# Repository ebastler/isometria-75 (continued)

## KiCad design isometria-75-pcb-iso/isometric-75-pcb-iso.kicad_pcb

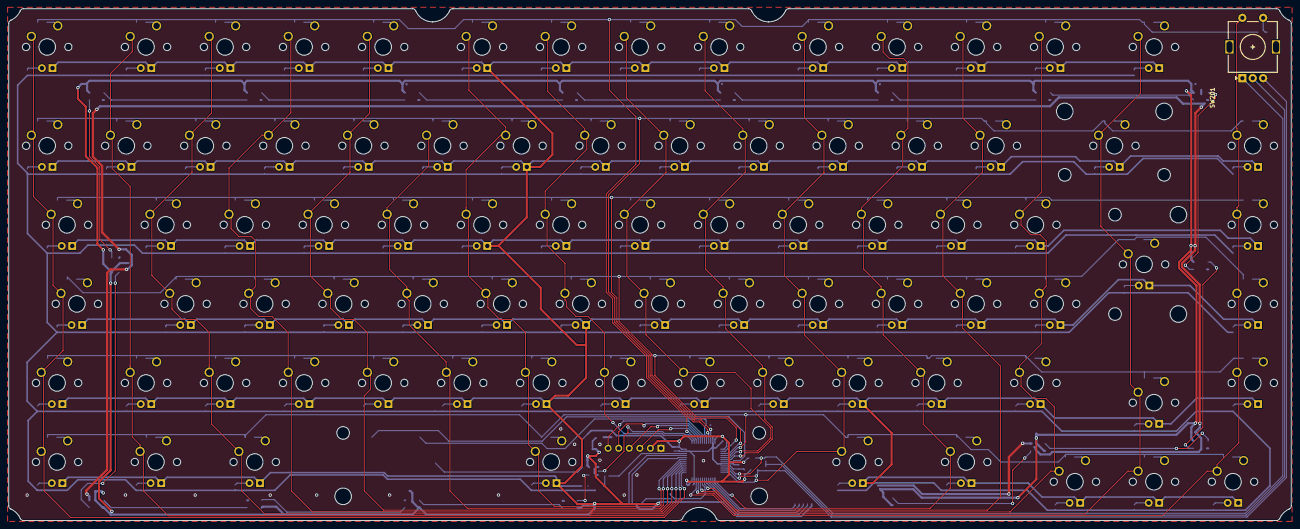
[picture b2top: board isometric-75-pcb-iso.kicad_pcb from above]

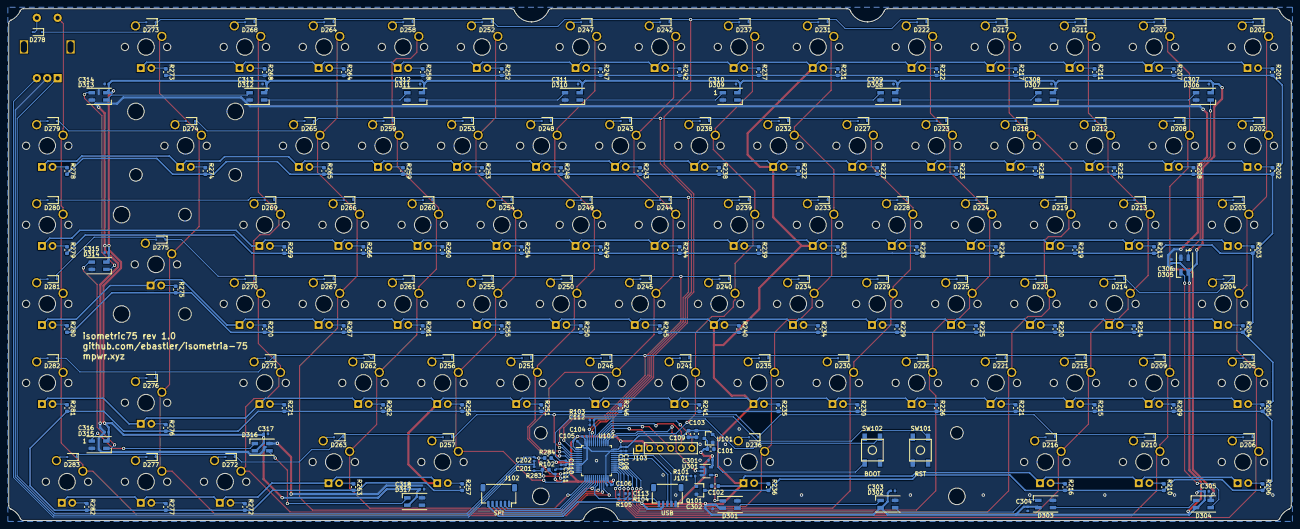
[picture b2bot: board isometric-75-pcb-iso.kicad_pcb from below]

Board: 2 copper layers, 308.3 x 123.0 mm, 314 parts (231 on the bottom side), 228 nets.

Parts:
C101, C102, C103, C109: 1u; C_0603_1608Metric
C104, C105, C106, C107, C110, C111, C112, C113, C201, C202, C301, C302, C303, C304, C305, C306, C307, C308, C309, C310, C311, C312, C313, C314, C315, C316, C317, C318: 100n; C_0402_1005Metric
C108: 1u; C_0402_1005Metric
D201, D202, D203, D204, D205, D206, D207, D208, D209, D210, D211, D212, D213, D214, D215, D216, D217, D218, D219, D220, D221, D222, D223, D224, D225, D226, D227, D228, D229, D230, D231, D232, D233, D234, D235, D236, D237, D238, D239, D240, D241, D242, D243, D244, D245, D246, D247, D248, D249, D250, D251, D252, D253, D254, D255, D256, D257, D258, D259, D260, D261, D262, D263, D264, D265, D266, D267, D268, D269, D270, D271, D272, D273, D274, D275, D276, D277, D278, D279, D280, D281, D282, D283: 1N4148; D_SOD-323F
D301, D302, D303, D304, D305, D306, D307, D308, D309, D310, D311, D312, D313, D314, D315, D316, D317: SK6812MINI; LED_SK6812MINI_PLCC4_3.5x3.5mm_P1.75mm
J101: USB; JST_SH_SM05B-SRSS-TB_1x05-1MP_P1.00mm_Horizontal
J102: SPI; JST_SH_SM06B-SRSS-TB_1x06-1MP_P1.00mm_Horizontal
J103: Conn_01x06_Male; PinHeader_1x06_P2.54mm_Vertical
MX201, MX202, MX207, MX208, MX209, MX211, MX212, MX213, MX214, MX215, MX217, MX218, MX219, MX220, MX221, MX222, MX223, MX224, MX225, MX226, MX227, MX228, MX229, MX230, MX231, MX232, MX233, MX234, MX235, MX237, MX238, MX239, MX240, MX241, MX242, MX243, MX244, MX245, MX246, MX247, MX248, MX249, MX250, MX251, MX252, MX253, MX254, MX255, MX256, MX258, MX259, MX260, MX261, MX262, MX264, MX265, MX266, MX267, MX268, MX269, MX270, MX272, MX273, MX276, MX277, MX278, MX279, MX280, MX281, MX282: MX-LED; MXOnly-1U
MX203, MX257, MX271: MX-LED; MXOnly-1.5U
MX204: MX-LED; MXOnly-1.75U
MX205, MX206, MX210, MX216, MX263: MX-LED; MXOnly-1.25U
MX236: MX-LED; MXOnly-6.25U
MX274: MX-LED; MXOnly-2U-ReversedStabilizers
MX275: MX-LED; MXOnly-ISO
Q101: AO3400A; SOT-23
R101, R102: 100; R_0402_1005Metric
R103: 10k; R_0402_1005Metric
R104, R105: 50k; R_0402_1005Metric
R201, R202, R203, R204, R205, R206, R207, R208, R209, R210, R211, R212, R213, R214, R215, R216, R217, R218, R219, R220, R221, R222, R223, R224, R225, R226, R227, R228, R229, R230, R231, R232, R233, R234, R235, R236, R237, R238, R239, R240, R241, R242, R243, R244, R245, R246, R247, R248, R249, R250, R251, R252, R253, R254, R255, R256, R257, R258, R259, R260, R261, R262, R263, R264, R265, R266, R267, R268, R269, R270, R271, R272, R273, R274, R275, R276, R277, R278, R279, R280, R281, R282: 680; R_0603_1608Metric
R283, R284: 10k; R_0603_1608Metric
SW101: RST; SKQG-1155865
SW102: BOOT; SKQG-1155865
SW201: Rotary_Encoder_Switch; RotaryEncoder_Alps_EC11E-Switch_Vertical_H20mm
U101: XC6206P332MR; SOT-23
U102: STM32F072CBTx; LQFP-48_7x7mm_P0.5mm
U301: 74LVC1G125; SOT-23-5

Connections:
+3V3: C103.1, C104.1, C105.1, C106.1, C107.1, C108.1, C109.1, J103.2, R102.1, R283.1, R284.2, SW102.1, U101.2, U102.1, U102.24, U102.36, U102.48
+5V: C101.1, C102.1, C301.1, C302.1, C303.1, C304.1, C305.1, C306.1, C307.1, C308.1, C309.1, C310.1, C311.1, C312.1, C313.1, C314.1, C315.1, C316.1, C317.1, C318.1, D301.4, D302.4, D303.4, D304.4, D305.4, D306.4, D307.4, D308.4, D309.4, D310.4, D311.4, D312.4, D313.4, D314.4, D315.4, D316.4, D317.4, J101.4, J102.6, MX201.4, MX202.4, MX203.4, MX204.4, MX205.4, MX206.4, MX207.4, MX208.4, MX209.4, MX210.4, MX211.4, MX212.4, MX213.4, MX214.4, MX215.4, MX216.4, MX217.4, MX218.4, MX219.4, MX220.4, MX221.4, MX222.4, MX223.4, MX224.4, MX225.4, MX226.4, MX227.4, MX228.4, MX229.4, MX230.4, MX231.4, MX232.4, MX233.4, MX234.4, MX235.4, MX236.4, MX237.4, MX238.4, MX239.4, MX240.4, MX241.4, MX242.4, MX243.4, MX244.4, MX245.4, MX246.4, MX247.4, MX248.4, MX249.4, MX250.4, MX251.4, MX252.4, MX253.4, MX254.4, MX255.4, MX256.4, MX257.4, MX258.4, MX259.4, MX260.4, MX261.4, MX262.4, MX263.4, MX264.4, MX265.4, MX266.4, MX267.4, MX268.4, MX269.4, MX270.4, MX271.4, MX272.4, MX273.4, MX274.4, MX275.4, MX276.4, MX277.4, MX278.4, MX279.4, MX280.4, MX281.4, MX282.4, U101.3, U301.5
COL0: MX201.1, MX202.1, MX203.1, MX204.1, MX205.1, MX206.1, U102.25
COL1: MX207.1, MX208.1, MX209.1, MX210.1, U102.26
COL2: MX211.1, MX212.1, MX213.1, MX214.1, MX215.1, MX216.1, U102.27
COL3: MX217.1, MX218.1, MX219.1, MX220.1, MX221.1, U102.28
COL4: MX222.1, MX223.1, MX224.1, MX225.1, MX226.1, U102.29
COL5: MX227.1, MX228.1, MX229.1, MX230.1, U102.30
COL6: MX231.1, MX232.1, MX233.1, MX234.1, MX235.1, MX236.1, U102.31
COL7: MX237.1, MX238.1, MX239.1, MX240.1, MX241.1, U102.37
COL8: MX242.1, MX243.1, MX244.1, MX245.1, MX246.1, U102.5
COL9: MX247.1, MX248.1, MX249.1, MX250.1, MX251.1, U102.6
COL10: MX252.1, MX253.1, MX254.1, MX255.1, MX256.1, MX257.1, U102.12
COL11: MX258.1, MX259.1, MX260.1, MX261.1, MX262.1, MX263.1, U102.13
COL12: MX264.1, MX265.1, MX266.1, MX267.1, U102.18
COL13: MX268.1, MX269.1, MX270.1, MX271.1, MX272.1, U102.20
COL14: MX273.1, MX274.1, MX275.1, MX276.1, MX277.1, U102.21
COL15: MX278.1, MX279.1, MX280.1, MX281.1, MX282.1, SW201.S2, U102.22
GND: C101.2, C102.2, C103.2, C104.2, C105.2, C106.2, C107.2, C108.2, C109.2, C110.2, C111.2, C112.2, C113.2, C201.1, C202.2, C301.2, C302.2, C303.2, C304.2, C305.2, C306.2, C307.2, C308.2, C309.2, C310.2, C311.2, C312.2, C313.2, C314.2, C315.2, C316.2, C317.2, C318.2, D301.2, D302.2, D303.2, D304.2, D305.2, D306.2, D307.2, D308.2, D309.2, D310.2, D311.2, D312.2, D313.2, D314.2, D315.2, D316.2, D317.2, J101.1, J102.1, J103.1, Q101.2, R103.2, R105.2, SW101.1, SW201.C, U101.1, U102.8, U102.23, U102.35, U102.47, U301.1, U301.3
LED-: Q101.3, R201.2, R202.2, R203.2, R204.2, R205.2, R206.2, R207.2, R208.2, R209.2, R210.2, R211.2, R212.2, R213.2, R214.2, R215.2, R216.2, R217.2, R218.2, R219.2, R220.2, R221.2, R222.2, R223.2, R224.2, R225.2, R226.2, R227.2, R228.2, R229.2, R230.2, R231.2, R232.2, R233.2, R234.2, R235.2, R236.2, R237.2, R238.2, R239.2, R240.2, R241.2, R242.2, R243.2, R244.2, R245.2, R246.2, R247.2, R248.2, R249.2, R250.2, R251.2, R252.2, R253.2, R254.2, R255.2, R256.2, R257.2, R258.2, R259.2, R260.2, R261.2, R262.2, R263.2, R264.2, R265.2, R266.2, R267.2, R268.2, R269.2, R270.2, R271.2, R272.2, R273.2, R274.2, R275.2, R276.2, R277.2, R278.2, R279.2, R280.2, R281.2, R282.2
LED_PWM: R101.1, U102.34
unnamed: C110.1, SW101.2, U102.7
unnamed: C111.1, R102.2, U102.9
unnamed: C112.1, R103.1, SW102.2, U102.44
unnamed: C113.1, R104.2, R105.1, U102.19
unnamed: D201.2, MX201.2
unnamed: D202.2, MX202.2
unnamed: D203.2, MX203.2
unnamed: D204.2, MX204.2
unnamed: D205.2, MX205.2
unnamed: D206.2, MX206.2
unnamed: D207.2, MX207.2
unnamed: D208.2, MX208.2
unnamed: D209.2, MX209.2
unnamed: D210.2, MX210.2
unnamed: D211.2, MX211.2
unnamed: D212.2, MX212.2
unnamed: D213.2, MX213.2
unnamed: D214.2, MX214.2
unnamed: D215.2, MX215.2
unnamed: D216.2, MX216.2
unnamed: D217.2, MX217.2
unnamed: D218.2, MX218.2
unnamed: D219.2, MX219.2
unnamed: D220.2, MX220.2
unnamed: D221.2, MX221.2
unnamed: D222.2, MX222.2
unnamed: D223.2, MX223.2
unnamed: D224.2, MX224.2
unnamed: D225.2, MX225.2
unnamed: D226.2, MX226.2
unnamed: D227.2, MX227.2
unnamed: D228.2, MX228.2
unnamed: D229.2, MX229.2
unnamed: D230.2, MX230.2
unnamed: D231.2, MX231.2
unnamed: D232.2, MX232.2
unnamed: D233.2, MX233.2
unnamed: D234.2, MX234.2
unnamed: D235.2, MX235.2
unnamed: D236.2, MX236.2
unnamed: D237.2, MX237.2
unnamed: D238.2, MX238.2
unnamed: D239.2, MX239.2
unnamed: D240.2, MX240.2
unnamed: D241.2, MX241.2
unnamed: D242.2, MX242.2
unnamed: D243.2, MX243.2
unnamed: D244.2, MX244.2
unnamed: D245.2, MX245.2
unnamed: D246.2, MX246.2
unnamed: D247.2, MX247.2
unnamed: D248.2, MX248.2
unnamed: D249.2, MX249.2
unnamed: D250.2, MX250.2
unnamed: D251.2, MX251.2
unnamed: D252.2, MX252.2
unnamed: D253.2, MX253.2
unnamed: D254.2, MX254.2
unnamed: D255.2, MX255.2
unnamed: D256.2, MX256.2
unnamed: D257.2, MX257.2
unnamed: D258.2, MX258.2
unnamed: D259.2, MX259.2
unnamed: D260.2, MX260.2
unnamed: D261.2, MX261.2
unnamed: D262.2, MX262.2
unnamed: D263.2, MX263.2
unnamed: D264.2, MX264.2
unnamed: D265.2, MX265.2
unnamed: D266.2, MX266.2
unnamed: D267.2, MX267.2
unnamed: D268.2, MX268.2
unnamed: D269.2, MX269.2
unnamed: D270.2, MX270.2
unnamed: D271.2, MX271.2
unnamed: D272.2, MX272.2
unnamed: D273.2, MX273.2
unnamed: D274.2, MX274.2
unnamed: D275.2, MX275.2
unnamed: D276.2, MX276.2
unnamed: D277.2, MX277.2
unnamed: D278.2, SW201.S1
unnamed: D279.2, MX278.2
unnamed: D280.2, MX279.2
unnamed: D281.2, MX280.2
unnamed: D282.2, MX281.2
unnamed: D283.2, MX282.2
unnamed: D301.1, D302.3
unnamed: D301.3, U301.4
unnamed: D302.1, D303.3
unnamed: D303.1, D304.3
unnamed: D304.1, D305.3
unnamed: D305.1, D306.3
unnamed: D306.1, D307.3
unnamed: D307.1, D308.3
unnamed: D308.1, D309.3
unnamed: D309.1, D310.3
unnamed: D310.1, D311.3
unnamed: D311.1, D312.3
unnamed: D312.1, D313.3
unnamed: D313.1, D314.3
unnamed: D314.1, D315.3
unnamed: D315.1, D316.3
unnamed: D316.1, D317.3
unnamed: MX201.3, R201.1
unnamed: MX202.3, R202.1
unnamed: MX203.3, R203.1
unnamed: MX204.3, R204.1
unnamed: MX205.3, R205.1
unnamed: MX206.3, R206.1
unnamed: MX207.3, R207.1
unnamed: MX208.3, R208.1
unnamed: MX209.3, R209.1
unnamed: MX210.3, R210.1
unnamed: MX211.3, R211.1
unnamed: MX212.3, R212.1
unnamed: MX213.3, R213.1
unnamed: MX214.3, R214.1
unnamed: MX215.3, R215.1
unnamed: MX216.3, R216.1
unnamed: MX217.3, R217.1
unnamed: MX218.3, R218.1
unnamed: MX219.3, R219.1
unnamed: MX220.3, R220.1
unnamed: MX221.3, R221.1
unnamed: MX222.3, R222.1
unnamed: MX223.3, R223.1
unnamed: MX224.3, R224.1
unnamed: MX225.3, R225.1
unnamed: MX226.3, R226.1
unnamed: MX227.3, R227.1
unnamed: MX228.3, R228.1
unnamed: MX229.3, R229.1
unnamed: MX230.3, R230.1
unnamed: MX231.3, R231.1
unnamed: MX232.3, R232.1
unnamed: MX233.3, R233.1
unnamed: MX234.3, R234.1
unnamed: MX235.3, R235.1
unnamed: MX236.3, R236.1
unnamed: MX237.3, R237.1
unnamed: MX238.3, R238.1
unnamed: MX239.3, R239.1
unnamed: MX240.3, R240.1
unnamed: MX241.3, R241.1
unnamed: MX242.3, R242.1
unnamed: MX243.3, R243.1
unnamed: MX244.3, R244.1
unnamed: MX245.3, R245.1
unnamed: MX246.3, R246.1
unnamed: MX247.3, R247.1
unnamed: MX248.3, R248.1
unnamed: MX249.3, R249.1
unnamed: MX250.3, R250.1
unnamed: MX251.3, R251.1
unnamed: MX252.3, R252.1
unnamed: MX253.3, R253.1
unnamed: MX254.3, R254.1
unnamed: MX255.3, R255.1
unnamed: MX256.3, R256.1
unnamed: MX257.3, R257.1
unnamed: MX258.3, R258.1
unnamed: MX259.3, R259.1
unnamed: MX260.3, R260.1
unnamed: MX261.3, R261.1
unnamed: MX262.3, R262.1
unnamed: MX263.3, R263.1
unnamed: MX264.3, R264.1
unnamed: MX265.3, R265.1
unnamed: MX266.3, R266.1
unnamed: MX267.3, R267.1
unnamed: MX268.3, R268.1
unnamed: MX269.3, R269.1
unnamed: MX270.3, R270.1
unnamed: MX271.3, R271.1
unnamed: MX272.3, R272.1
unnamed: MX273.3, R273.1
unnamed: MX274.3, R274.1
unnamed: MX275.3, R275.1
unnamed: MX276.3, R276.1
unnamed: MX277.3, R277.1
unnamed: MX278.3, R278.1
unnamed: MX279.3, R279.1
unnamed: MX280.3, R280.1
unnamed: MX281.3, R281.1
unnamed: MX282.3, R282.1
unnamed: Q101.1, R101.2
PB4: J103.3, U102.40
PB5: J103.4, U102.41
PB6_TX1: J103.5, U102.42
PB7_RX1: J103.6, U102.43
ROTA: C201.2, R283.2, SW201.B, U102.11
ROTB: C202.1, R284.1, SW201.A, U102.10
ROW0: D201.1, D207.1, D211.1, D217.1, D222.1, D231.1, D237.1, D242.1, D247.1, D252.1, D258.1, D264.1, D268.1, D273.1, D278.1, U102.39
ROW1: D202.1, D208.1, D212.1, D218.1, D223.1, D227.1, D232.1, D238.1, D243.1, D248.1, D253.1, D259.1, D265.1, D274.1, D279.1, U102.45
ROW2: D203.1, D213.1, D219.1, D224.1, D228.1, D233.1, D239.1, D244.1, D249.1, D254.1, D260.1, D266.1, D269.1, D280.1, U102.46
ROW3: D204.1, D214.1, D220.1, D225.1, D229.1, D234.1, D240.1, D245.1, D250.1, D255.1, D261.1, D267.1, D270.1, D275.1, D281.1, U102.2
ROW4: D205.1, D209.1, D215.1, D221.1, D226.1, D230.1, D235.1, D241.1, D246.1, D251.1, D256.1, D262.1, D271.1, D276.1, D282.1, U102.3
ROW5: D206.1, D210.1, D216.1, D236.1, D257.1, D263.1, D272.1, D277.1, D283.1, U102.4
SPI_MISO: J102.4, U102.16
SPI_MOSI: J102.5, U102.17
SPI_NSS: J102.2, U102.14
SPI_SCK: J102.3, U102.15
UGLED: U102.38, U301.2
USB-D+: J101.2, U102.33
USB-D-: J101.3, U102.32
Vsense: J101.5, R104.1

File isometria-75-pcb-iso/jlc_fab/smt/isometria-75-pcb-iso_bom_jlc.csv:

"Comment","Designator","Footprint","LCSC Part #"
"100uF","C102,C101","CP_EIA-3528-21_Kemet-B","C16133"
"10uF","C103","CP_EIA-3216-18_Kemet-A","C7171"
"1uF","C106,C104","C_0402_1005Metric","C52923"
"4.7uF","C111,C105,C112","C_0402_1005Metric","C23733"
"100nF","C114,C113,C117,C110,C109,C108,C107,C115,C116,C202,C201,C302,C303,C304,C305,C307,C308,C309,C310,C311,C312,C301,C313,C314,C315,C316,C317,C318,C306","C_0402_1005Metric","C1525"
"1N4148","D202,D203,D204,D205,D206,D208,D209,D210,D212,D213,D214,D215,D216,D218,D219,D220,D221,D223,D224,D225,D226,D227,D228,D229,D230,D232,D233,D234,D235,D236,D238,D239,D240,D241,D243,D244,D245,D246,D248,D249,D250,D251,D253,D254,D255,D256,D257,D259,D260,D261,D262,D263,D265,D266,D267,D269,D270,D271,D272,D274,D275,D276,D277,D279,D280,D281,D282,D283,D278,D273,D268,D264,D258,D252,D247,D242,D237,D231,D222,D217,D211,D207,D201","D_SOD-323F","C2128"
"AO3400A","Q101","SOT-23","C20917"
"100R","R101","R_0402_1005Metric","C25076"
"10R","R102","R_0402_1005Metric","C25077"
"10k","R103,R283,R284","R_0402_1005Metric","C25744"
"47k","R107,R106,R104,R105","R_0402_1005Metric","C25792"
"680R","R201,R202,R203,R204,R205,R206,R207,R208,R209,R210,R211,R212,R213,R214,R215,R216,R217,R218,R219,R220,R221,R222,R223,R224,R225,R226,R227,R228,R229,R230,R231,R232,R233,R234,R235,R236,R237,R238,R239,R240,R241,R242,R243,R244,R245,R246,R247,R248,R249,R250,R251,R252,R253,R254,R255,R256,R257,R258,R259,R260,R261,R262,R263,R264,R265,R266,R267,R268,R269,R270,R271,R272,R273,R274,R275,R276,R277,R278,R279,R280,R281,R282","R_0603_1608Metric","C23228"
"RST","SW101","SKQG-1155865","C318886"
"BOOT","SW102","SKQG-1155865","C318886"
"XC6206P332MR","U101","SOT-23","C5446"
"STM32F072CBTx","U102","LQFP-48_7x7mm_P0.5mm","C81720"
"74LVC1G125","U301","SOT-23-5","C23654"

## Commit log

2020-03-05 added license/readme
2020-03-05 initialize project
2020-03-05 Add submodules
2020-03-05 Add footprint libraries
2020-03-05 finished mc schematic
2020-03-05 added jst submodule
2020-03-05 added key matrix
2020-03-05 minor schematic changes
2020-03-06 assigned footprints
2020-03-06 placing switches
2020-03-07 wired switches and leds
2020-03-08 continued the pcb
2020-03-12 more pcb wiring
2020-03-13 connecting rows
2020-03-13 finished wiring cols, changed jlc connector color
2020-03-14 added underglow
2020-03-14 added ground planes, various minor fixes
2020-03-15 cosmethical changes, fixed a footprint collision
2020-03-15 added two render images
2020-03-15 fixed link
2020-03-15 updated readme once more
2020-03-15 fixed a typo
2020-03-15 changed divider resistors to save power
2020-03-19 minor layout improvements
2020-03-19 updated renders
2020-03-19 changed formatting
2020-03-19 minor readme changes
2020-03-24 minor layout fixes (thanks gLu3xb3rchi)
2020-03-24 renamed +5V net (thanks gLu3xb3rchi)
2020-03-26 changed switch footprint to accomodate millmax 7305
2020-03-26 updated a render
2020-03-26 changed readme
2020-03-29 added pcb cutouts for mounting
2020-03-29 renamed folder
2020-03-29 renamed pcb file, added 3d models
2020-03-29 updated paths
2020-03-29 re-adding submodules
2020-03-29 rewired leds for better pcb edge clearance
2020-03-29 silkscreen improvements
2020-03-29 changed led backlight to a different pin
2020-03-29 moved UGLED to a HW PWM pin, improved some trace routing
2020-03-29 remove unused 3d model
2020-03-29 replaced a 3d model
2020-03-30 moved underglow from TIM1 to TIM2
2020-03-30 major schematic/pcb rework
    rewired SPI, added SPI CS/IRQ/RES pins, rewired part of the matrix in the process
    changed to a larger header for SPI
    added a divider for input voltage sensing
    removed extension header due to a lack of remaining unused GPIOs
2020-03-30 Update fp-info-cache
2020-03-31 added capacity, rerouted power traces
2020-03-31 cosmetic silkscreen fixes
2020-03-31 fixed a groundplane error
2020-03-31 deleted unused text in the schematic
2020-03-31 routed an unused GPIO to a solder pad
    could be used for possible expansion
2020-04-02 minor changes
2020-04-08 matched usb trace length
2020-04-13 added .bak
2020-04-13 some minor routing improvements
2020-04-13 moved power symbols
2020-04-15 added a link
2020-04-15 rerouted some traces
2020-04-15 moved some traces
2020-04-15 Create fp-info-cache
2020-04-15 improved routing in a few places
2020-04-16 new renders
2020-04-16 update file name
2020-04-16 changed table
2020-04-19 fixed silkscreen labels
2020-04-20 numerous minor improvements and fixes
2020-04-20 silkscreen fixes
2020-04-26 final touches
    changed some 0603 to 0402 for consistency, added vias to properly better ground planes, added LCSC part numbers for jlcpcb assembly
2020-04-26 moved silkscreen from vias
2020-04-27 improved componend value formatting
2020-04-27 added manufacturing files
2020-04-27 added BOM file
2020-05-01 added 3d models
2020-05-09 moved render models to subfolder
2020-05-09 added step + drawing for manufacturing
2020-05-17 fixed label directions
2020-07-18 added submodule
2020-07-18 removed wrong submodule
2020-07-18 changed regulator symbol to submodule
2020-07-18 removed out-of-sync submodule
2020-07-18 re-added submodule
2020-07-18 updated submodules
2020-10-11 changed gitignore
2020-10-11 cleaned up submodules
2020-10-11 removed unneccesary folder
2020-10-11 fixed minor bugs, migrated to new libs
2020-10-11 added branding submodule
2020-10-11 updated submodule
2020-10-11 added logo to pcb
2020-10-11 fixed ignore paths
2020-10-12 updated rev numbering
2020-10-12 updated gerbers, removed outdated PCBA
2020-10-15 started nRF v2 rework
2020-10-17 continued routing
2020-10-23 began renaming project
2020-10-23 renamed project
2020-10-23 added gerbers
2020-10-24 minor routing changes
2020-10-24 added v2 pcb folder to gitignore of master
2020-10-24 removed unused renders, updated PCB renders
2020-11-04 final checks
2020-11-05 removed silkscreen labels from obvious components
2020-11-05 added prototyping gerbers
2020-12-14 no clue
2020-12-17 added v1 VIA json
